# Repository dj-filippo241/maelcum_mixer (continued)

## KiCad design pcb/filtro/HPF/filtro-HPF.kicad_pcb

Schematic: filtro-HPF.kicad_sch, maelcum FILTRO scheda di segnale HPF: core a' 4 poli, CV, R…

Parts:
C1, C2: 220u 35V; CP_Radial_D8.0mm_P3.50mm
C3: 47u 10V; CP_Radial_D5.0mm_P2.00mm
C4, C8: 10u 35V; CP_Radial_D5.0mm_P2.00mm
C5, C9: 47u 35V; CP_Radial_D6.3mm_P2.50mm
C6, C10: 470u 25V; CP_Radial_D8.0mm_P3.50mm
C7, C11: 100u 25V; CP_Radial_D6.3mm_P2.50mm
C12, C13: 1u 50V; C_1206_3216Metric
C14, C15: 1u 25V; C_1206_3216Metric
C16, C17, C19, C20: 4u7 25V; C_1206_3216Metric
C18, C21: 10u 25V; C_1206_3216Metric
C22: 1u; C_1206_3216Metric
C23, C24, C25, C26, C31, C32, C33, C34, C35, C36, C37, C38, C40, C41, C44, C45, C48, C49, C50, C51, C52, C53, C54, C55, C57, C58, C61, C62, C65, C66, C67, C68, C69, C70, C71, C72, C77, C78, C79, C80, C81, C82, C83, C84, C85, C86: 100n; C_0805_2012Metric
C27, C28, C29, C30: 1n C0G; C_1206_3216Metric
C39, C56: 10p C0G; C_0805_2012Metric
C42, C43, C46, C47, C59, C60, C63, C64: 1n1 C0G; C_1206_3216Metric
C73, C75: 22u NP; CP_Radial_D6.3mm_P2.50mm
C74, C76: 47n film; C_1812_4532Metric
D1, D3, D6, D7, D8, D9, D10, D11, D12, D13, D14, D15, D16, D17, D18, D19, D20, D21, D22, D23, D24, D25, D26, D27, D28, D29, D30: 1N4148W; D_SOD-123
D2, D4: S1G; D_SMA
D5: LM4040-5.0; SOT-23
D31, D32, D33, D34: BAT54WS; D_SOD-323
FB1, FB2, FB3, FB4, FB5: ferrite 600R; L_1206_3216Metric
H1, H2, H3: CHASSIS; MountingHole_3.2mm_M3_Pad
J1: C96 maschio; DIN41612_C_3x32_Male_Horizontal_THT
J2: 2x6 cavo piatto; PinHeader_2x06_P2.54mm_Vertical
Q1, Q2, Q3, Q4: THAT320S14-U; SOIC-14_3.9x8.7mm_P1.27mm
Q5, Q6, Q7, Q8: MMBT3906; SOT-23
Q140: BD139; TO-126-3_Vertical
Q141: BD140; TO-126-3_Vertical
R1, R4: 120 1%; R_0805_2012Metric
R2, R5: 1k74 1%; R_0805_2012Metric
R3, R6, R96, R109: 1k; R_0805_2012Metric
R7, R8: 150k 0.1%; R_0805_2012Metric
R9: 1k5; R_0805_2012Metric
R10, R11, R16, R17, R19, R34, R37, R38, R42, R43, R48, R49, R50, R51, R52, R58, R59, R60, R66, R67, R68, R69, R70, R76, R77, R78, R84, R87, R89, R91, R92, R93, R97, R100, R102, R104, R105, R106: 10k 0.1%; R_0805_2012Metric
R12, R41, R95, R108, R110, R111, R112, R113, R114: 100k; R_0805_2012Metric
R13: 9k53 0.1%; R_0805_2012Metric
R14: 17k8 0.1%; R_0805_2012Metric
R15: 21k5 0.1%; R_0805_2012Metric
R18: 8k87 0.1%; R_0805_2012Metric
R20, R32: 24k3 0.1%; R_0805_2012Metric
R21: 1k +3300ppm/K; R_1206_3216Metric
R22, R24, R26, R28: 150 0.1%; R_0805_2012Metric
R23, R25, R27, R29, R86, R99: 2k2; R_0805_2012Metric
R30, R90, R94, R103, R107: 1M; R_0805_2012Metric
R31: 34k 0.1%; R_0805_2012Metric
R33: 113k 0.1%; R_0805_2012Metric
R35: 18k2 0.1%; R_0805_2012Metric
R36: 95k3 0.1%; R_0805_2012Metric
R39: 100k 0.1%; R_0805_2012Metric
R40: 34k8 0.1%; R_0805_2012Metric
R44, R45, R46, R47: 41k7 0.1%; R_0805_2012Metric
R53, R71: 5k41 0.1%; R_0805_2012Metric
R54, R56, R61, R63, R72, R74, R79, R81: 2k87 0.1%; R_0805_2012Metric
R55, R57, R62, R64, R73, R75, R80, R82: 100 0.1%; R_0805_2012Metric
R65, R83: 4k7; R_0805_2012Metric
R85, R98: 20k 0.1%; R_0805_2012Metric
R88, R101: 8k56 0.1%; R_0805_2012Metric
RV1: 1k; Potentiometer_Bourns_3266W_Vertical
RV2: 5k; Potentiometer_Bourns_3266W_Vertical
RV3, RV4, RV5, RV6: 100; Potentiometer_Bourns_3266W_Vertical
RV7: 10k; Potentiometer_Bourns_3266W_Vertical
U1, U8, U9, U14, U15, U20, U21, U22, U23, U24: OPA1654AIDR; SOIC-14_3.9x8.7mm_P1.27mm
U2, U3, U4, U5: LM334SM; SOIC-8_3.9x4.9mm_P1.27mm
U6, U7, U25: OPA1642AIDR; SOIC-8_3.9x4.9mm_P1.27mm
U10, U16, U146: OPA1612AIDR; SOIC-8_3.9x4.9mm_P1.27mm
U11, U12, U13, U17, U18, U19: LM13700M; SOIC-16_3.9x9.9mm_P1.27mm
U26: ADG1434YRUZ; TSSOP-20_4.4x6.5mm_P0.65mm
U140: LM317; TO-220-3_Vertical
U141: LM337; TO-220-3_Vertical
U142: 78L15; SOT-89-3
U143: 79L15; SOT-89-3
U144: LT3045EMSE; MSOP-12-1EP_3x4.039mm_P0.65mm_EP1.651x2.845mm
U145: LT3094EMSE; MSOP-12-1EP_3x4.039mm_P0.65mm_EP1.651x2.845mm

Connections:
+5V: FB5.1, J1.a21, J1.a22
+5VF: C3.1, FB5.2
+15LN: C18.1, C23.1, C25.1, C31.1, C33.1, C35.1, C37.1, C44.1, C48.1, C50.1, C52.1, C54.1, C61.1, C65.1, C67.1, C69.1, C71.1, R9.1, U1.4 (V+), U6.8 (V+), U7.8 (V+), U8.4 (V+), U9.4 (V+), U11.11 (V+), U12.11 (V+), U13.11 (V+), U14.4 (V+), U15.4 (V+), U17.11 (V+), U18.11 (V+), U19.11 (V+), U20.4 (V+), U21.4 (V+), U144.10 (OUTS), U144.11 (OUT), U144.12 (OUT), U146.8 (V+)
+15SW: C14.1, C85.1, U26.16 (VDD), U142.1 (OUT)
+18V: C7.1, C17.1, C40.1, C57.1, C77.1, C79.1, C81.1, C83.1, Q140.1 (E), U10.8 (V+), U16.8 (V+), U22.4 (V+), U23.4 (V+), U24.4 (V+), U25.8 (V+), U144.1 (IN), U144.2 (IN), U144.3 (IN), U144.4 (EN/UV), U144.7 (PGFB)
+REF5: J2.3, J2.12, R10.1, R18.1, R30.2, R36.1, U146.1, U146.2 (-)
-15LN: C21.2, C24.2, C26.2, C32.2, C34.2, C36.2, C38.2, C45.2, C49.2, C51.2, C53.2, C55.2, C62.2, C66.2, C68.2, C70.2, C72.2, RV3.2, RV3.3, RV4.2, RV4.3, RV5.2, RV5.3, RV6.2, RV6.3, U1.11 (V-), U2.1 (V-), U3.1 (V-), U4.1 (V-), U5.1 (V-), U6.4 (V-), U7.4 (V-), U8.11 (V-), U9.11 (V-), U11.6 (V-), U12.6 (V-), U13.6 (V-), U14.11 (V-), U15.11 (V-), U17.6 (V-), U18.6 (V-), U19.6 (V-), U20.11 (V-), U21.11 (V-), U145.10 (OUTS), U145.11 (OUT), U145.12 (OUT), U146.4 (V-)
-15SW: C15.2, C86.2, U26.5 (VSS), U143.3 (VO)
-18V: C11.2, C20.2, C41.2, C58.2, C78.2, C80.2, C82.2, C84.2, Q141.1 (E), U10.4 (V-), U16.4 (V-), U22.11 (V-), U23.11 (V-), U24.11 (V-), U25.4 (V-), U145.1 (IN), U145.2 (IN), U145.3 (EN/UV), U145.5 (PGFB), U145.13 (IN)
-REF5: R11.2, R15.2, R33.2, R35.2, R39.1, U146.7
ADJ+: C4.1, D1.2 (A), R1.2, R2.1, U140.1 (ADJ)
ADJ-: C8.2, D3.1 (K), R4.2, R5.1, U141.1 (ADJ)
AGND: C1.2, C2.1, C4.2, C5.2, C6.2, C7.2, C8.1, C9.1, C10.1, C11.1, C12.2, C13.1, C14.2, C15.1, C16.2, C17.2, C18.2, C19.1, C20.1, C21.1, C22.2, C23.2, C24.1, C25.2, C26.1, C31.2, C32.1, C33.2, C34.1, C35.2, C36.1, C37.2, C38.1, C40.2, C41.1, C42.2, C43.2, C44.2, C45.1, C46.2, C47.2, C48.2, C49.1, C50.2, C51.1, C52.2, C53.1, C54.2, C55.1, C57.2, C58.1, C59.2, C60.2, C61.2, C62.1, C63.2, C64.2, C65.2, C66.1, C67.2, C68.1, C69.2, C70.1, C71.2, C72.1, C77.2, C78.1, C79.2, C80.1, C81.2, C82.1, C83.2, C84.1, C85.2, C86.1, D5.2 (A), D7.2 (A), D8.2 (A), D9.2 (A), D10.2 (A), D24.1 (K), D25.2 (A), D28.1 (K), D29.2 (A), J1.a13, J1.a14, J1.a15, J1.a16, J1.a17, J1.a18, J1.a19, J1.a20, J1.b3, J1.b6, J1.b9, J1.b12, J1.b15, J1.b18, J1.b21, J1.b24, J1.b27, J1.b30, J2.1, J2.5, J2.8, J2.11, Q1.4 (SUB), Q1.6 (B3), Q1.11 (SUB2), Q1.13 (B2), Q2.4 (SUB), Q2.6 (B3), Q2.11 (SUB2), Q2.13 (B2), Q3.4 (SUB), Q3.6 (B3), Q3.11 (SUB2), Q3.13 (B2), Q4.4 (SUB), Q4.6 (B3), Q4.11 (SUB2), Q4.13 (B2), R2.2, R5.2, R7.2, R8.2, R12.2, R21.2, R41.2, R44.2, R45.2, R46.2, R47.2, R55.2, R57.2, R62.2, R64.2, R73.2, R75.2, R80.2, R82.2, R90.2, R96.2, R103.2, R109.2, U1.5 (+), U1.10 (+), U6.3 (+), U6.5 (+), U7.3 (+), U7.5 (+), U8.5 (+), U8.10 (+), U8.12 (+), U10.3 (+), U11.4 (INN_A), U11.13 (INN_B), U12.4 (INN_A), U12.13 (INN_B), U13.4 (INN_A), U13.14 (INP_B), U14.3 (+), U14.12 (+), U15.10 (+), U15.12 (+), U16.3 (+), U17.4 (INN_A), U17.13 (INN_B), U18.4 (INN_A), U18.13 (INN_B), U19.4 (INN_A), U19.14 (INP_B), U20.3 (+), U20.12 (+), U21.10 (+), U21.12 (+), U22.3 (+), U22.10 (+), U23.5 (+), U23.12 (+), U24.10 (+), U24.12 (+), U25.3 (+), U25.5 (+), U26.4 (S1B), U26.6 (GND), U26.7 (S2B), U26.11 (IN3), U26.12 (S3A), U26.13 (D3), U26.14 (S3B), U26.17 (S4B), U26.18 (D4), U26.19 (S4A), U26.20 (IN4), U142.2 (GND), U143.1 (GND), U144.6 (ILIM), U144.9 (GND), U144.13 (GND), U145.6 (ILIM), U145.9 (GND), U146.5 (+)
AL: R85.2, R86.1, U22.1
AR: R98.2, R99.1, U23.7
ARR: D13.1 (K), D14.2 (A), U8.8
BASE+: C6.1, Q140.3 (B), R3.2
BASE-: C10.2, Q141.3 (B), R6.2
BKL1: R56.2, R57.1, U11.14 (INP_B)
BKL2: R63.2, R64.1, U12.14 (INP_B), U13.3 (INP_A), U13.13 (INN_B)
BKR1: R74.2, R75.1, U17.14 (INP_B)
BKR2: R81.2, R82.1, U18.14 (INP_B), U19.3 (INP_A), U19.13 (INN_B)
BPBL1: R53.1, R56.1, U14.6 (-), U14.7
BPBL2: R63.1, R65.1, U15.1, U15.2 (-)
BPBR1: R71.1, R74.1, U20.6 (-), U20.7
BPBR2: R81.1, R83.1, U21.1, U21.2 (-)
BPL1: C42.1, U11.5 (OUT_A), U14.5 (+)
BPL2: C46.1, U12.5 (OUT_A), U15.3 (+)
BPR1: C59.1, U17.5 (OUT_A), U20.5 (+)
BPR2: C63.1, U18.5 (OUT_A), U21.3 (+)
BRNL: Q6.1 (B), U9.7
BRNR: Q8.1 (B), U9.14
BRPL: Q5.1 (B), U9.1
BRPR: Q7.1 (B), U9.8
BUS_HPF_L: C39.2, J1.b1, R48.2, U10.2 (-)
BUS_HPF_R: C56.2, J1.b2, R66.2, U16.2 (-)
CHASSIS: H1.1, H2.1, H3.1, J1.a25, J1.a26
CRL1: C27.2, Q1.1 (C1), U2.3 (V+), U6.2 (-)
CRL2: C28.2, Q2.1 (C1), U3.3 (V+), U6.6 (-)
CRR1: C29.2, Q3.1 (C1), U4.3 (V+), U7.2 (-)
CRR2: C30.2, Q4.1 (C1), U5.3 (V+), U7.6 (-)
CTRL_GND: C3.2, J1.a23, J1.a24, J1.c16, J1.c20, J1.c24, J1.c28, R110.2, R111.2, R112.2, R113.2, R114.2
DNL: R87.2, R88.2, R89.1, U22.9 (-)
DNR: R100.2, R101.2, R102.1, U23.13 (-)
DWL: J2.7, R90.1, U22.12 (+)
DWR: J2.10, R103.1, U24.3 (+)
ERNL: Q6.2 (E), R45.1, U9.6 (-)
ERNR: Q8.2 (E), R47.1, U9.13 (-)
ERPL: Q5.2 (E), R44.1, U9.2 (-)
ERPR: Q7.2 (E), R46.1, U9.9 (-)
EXL1: D7.1 (K), Q1.3 (E1), Q1.5 (E3), Q1.12 (E2), R23.2
EXL2: D8.1 (K), Q2.3 (E1), Q2.5 (E3), Q2.12 (E2), R25.2
EXR1: D9.1 (K), Q3.3 (E1), Q3.5 (E3), Q3.12 (E2), R27.2
EXR2: D10.1 (K), Q4.3 (E1), Q4.5 (E3), Q4.12 (E2), R29.2
FILT_MODE1_0: D31.2 (A), J1.c1, R110.1
FILT_MODE2_0: D32.2 (A), J1.c3, R111.1
FILT_MODE3_0: D33.2 (A), J1.c5, R112.1
FILT_MODE4_0: D34.2 (A), J1.c7, R113.1
FW: J2.2, R12.1, U1.3 (+)
GNL: R84.2, R85.1, U22.2 (-)
GNR: R97.2, R98.1, U23.6 (-)
HKL1: R54.2, R55.1, U11.3 (INP_A)
HKL2: R61.2, R62.1, U12.3 (INP_A)
HKR1: R72.2, R73.1, U17.3 (INP_A)
HKR2: R79.2, R80.1, U18.3 (INP_A)
HPF_OUT_L: J1.b7, R49.2
HPF_OUT_R: J1.b8, R67.2
HPL1: R52.2, R54.1, R58.1, U14.1
HPL2: R60.2, R61.1, R84.1, R87.1, R92.1, U14.14
HPR1: R70.2, R72.1, R76.1, U20.1
HPR2: R78.2, R79.1, R97.1, R100.1, R105.1, U20.14
IAL1_1: Q1.14 (C2), U11.1 (IABC_A)
IAL1_2: Q1.7 (C3), U11.16 (IABC_B)
IAL2_1: Q2.14 (C2), U12.1 (IABC_A)
IAL2_2: Q2.7 (C3), U12.16 (IABC_B)
IAR1_1: Q3.14 (C2), U17.1 (IABC_A)
IAR1_2: Q3.7 (C3), U17.16 (IABC_B)
IAR2_1: Q4.14 (C2), U18.1 (IABC_A)
IAR2_2: Q4.7 (C3), U18.16 (IABC_B)
IRNL: Q6.3 (C), U13.16 (IABC_B)
IRNR: Q8.3 (C), U19.16 (IABC_B)
IRPL: Q5.3 (C), U13.1 (IABC_A)
IRPR: Q7.3 (C), U19.1 (IABC_A)
LPBL1: R51.1, U14.8, U14.9 (-)
LPBL2: R59.1, U15.6 (-), U15.7
LPBR1: R69.1, U20.8, U20.9 (-)
LPBR2: R77.1, U21.6 (-), U21.7
LPL1: C43.1, U11.12 (OUT_B), U14.10 (+)
LPL2: C47.1, U12.12 (OUT_B), U15.5 (+)
LPR1: C60.1, U17.12 (OUT_B), U20.10 (+)
LPR2: C64.1, U18.12 (OUT_B), U21.5 (+)
MUTEN: D31.1 (K), D32.1 (K), D33.1 (K), D34.1 (K), R114.1, U26.1 (IN1), U26.10 (IN2)
N1R: D11.2 (A), R32.2, R33.1
N2R: D12.2 (A), R34.2, R35.1
NHF: D6.2 (A), R14.2, R15.1
NIG: R42.2, R43.1, U8.13 (-)
NLAL: D15.1 (K), D16.2 (A)
NLAR: D19.1 (K), D20.2 (A)
NLBL: D17.1 (K), D18.2 (A)
NLBR: D21.1 (K), D22.2 (A)
NLL: D15.2 (A), D18.1 (K), R65.2
NLR: D19.2 (A), D22.1 (K), R83.2
NREF5I: R10.2, R11.1, U146.6 (-)
NSL1: R50.2, R51.2, R52.1, R53.2, U14.2 (-)
NSL2: D16.1 (K), D17.2 (A), R58.2, R59.2, R60.1, U13.5 (OUT_A), U13.12 (OUT_B), U14.13 (-)
NSR1: R68.2, R69.2, R70.1, R71.2, U20.2 (-)
NSR2: D20.1 (K), D21.2 (A), R76.2, R77.2, R78.1, U19.5 (OUT_A), U19.12 (OUT_B), U20.13 (-)
NU15_1: U15.8, U15.9 (-)
NU15_2: U15.13 (-), U15.14
NU21_1: U21.8, U21.9 (-)
NU21_2: U21.13 (-), U21.14
NU24_1: U24.8, U24.9 (-)
NU24_2: U24.13 (-), U24.14
NWF: R17.2, R19.1, RV1.2, RV1.3, U1.9 (-)
OD_L: R49.1, U10.6 (-), U10.7
OD_R: R67.1, U16.6 (-), U16.7
OLL1: C27.1, R23.1, U6.1
OLL2: C28.1, R25.1, U6.7
OLR1: C29.1, R27.1, U7.1
OLR2: C30.1, R29.1, U7.7
PTL: C73.2, J2.6
PTR: C75.2, J2.9
RAW+22: FB3.1, J1.a5, J1.a6
RAW+27: FB1.1, J1.a1, J1.a2
RAW-22: FB4.1, J1.a7, J1.a8
RAW-27: FB2.1, J1.a3, J1.a4
REF5K: C22.1, D5.1 (K), R9.2, U146.3 (+)
RRF: R36.2, RV7.1
RSF: R20.2, RV2.1
RSL1: R22.1, U2.2 (R)
RSL2: R24.1, U3.2 (R)
RSR1: R26.1, U4.2 (R)
RSR2: R28.1, U5.2 (R)
RTL1: R22.2, RV3.1
RTL2: R24.2, RV4.1
RTR1: R26.2, RV5.1
RTR2: R28.2, RV6.1
RW: J2.4, R30.1, U8.3 (+)
RX_L: C39.1, R48.1, R50.1, U10.1
RX_R: C56.1, R66.1, R68.1, U16.1
RZF: R18.2, RV1.1
SETN: C19.2, R8.1, U145.8 (SET)
SETP: C16.1, R7.1, U144.8 (SET)
SHF: R16.2, R17.1, U1.7
SIL: C74.1, R94.2, U25.2 (-)
SIR: C76.1, R107.2, U25.6 (-)
SJR: D11.1 (K), D12.1 (K), R31.2, R37.1, RV7.2, RV7.3, U8.6 (-)
SNL: R91.2, R92.2, R93.1, U23.2 (-)
SNR: R104.2, R105.2, R106.1, U24.6 (-)
SOL: C74.2, R95.1, U25.1
SOR: C76.2, R108.1, U25.7
SRR: D13.2 (A), R38.2, R39.2, R40.2, U8.9 (-)
V22F+: C12.1, FB3.2, U142.3 (IN)
V22F-: C13.2, FB4.2, U143.2 (VI)
V27F+: C1.1, D2.1 (K), FB1.2, U140.3 (VI)
V27F-: C2.2, D4.2 (A), FB2.2, U141.2 (VI)
VB1: Q1.2 (B1), Q2.2 (B1), Q3.2 (B1), Q4.2 (B1), U1.13 (-), U1.14
VBD: R21.1, RV2.2, RV2.3, U1.12 (+)
VDL: C73.1, R89.2, U22.8
VDR: C75.1, R102.2, U23.14
VGF: D6.1 (K), R13.2, R16.1, U1.6 (-)
VNG: D14.1 (K), R40.1, R41.1, R42.1
VNN: R43.2, U8.14, U9.5 (+), U9.12 (+)
VPL: R95.2, R96.1, U23.3 (+)
VPN: R37.2, U8.7, U9.3 (+), U9.10 (+)
VPR: R108.2, R109.1, U24.5 (+)
VREG+: C5.1, D1.1 (K), D2.2 (A), Q140.2 (C), R1.1, R3.1, U140.2 (VO)
VREG-: C9.2, D3.2 (A), D4.1 (K), Q141.2 (C), R4.1, R6.1, U141.3 (VO)
VXF: R13.1, R14.1, U1.1, U1.2 (-)
VXR: R31.1, R32.1, R34.1, R38.1, U8.1, U8.2 (-)
WBL: R88.1, U22.6 (-), U22.7
WBR: R101.1, U23.8, U23.9 (-)
WF: R19.2, R20.1, U1.8
WL: D23.2 (A), D26.1 (K), R86.2, U22.5 (+)
WOL: R91.1, U22.13 (-), U22.14
WOR: R104.1, U24.1, U24.2 (-)
WPL: D23.1 (K), D24.2 (A)
WPR: D27.1 (K), D28.2 (A)
WQL: D25.1 (K), D26.2 (A)
WQR: D29.1 (K), D30.2 (A)
WR: D27.2 (A), D30.1 (K), R99.2, U23.10 (+)
YL: R93.2, R94.1, U23.1, U26.2 (S1A)
YM_L: U10.5 (+), U26.3 (D1)
YM_R: U16.5 (+), U26.8 (D2)
YR: R106.2, R107.1, U24.7, U26.9 (S2A)

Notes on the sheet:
BACKPLANE C96 (classe FILTRO, sistema-backplane §4, dec. 159)
ALIMENTAZIONE +-18 audio, +-15 switch, +5, +-15 LN (core e CV), +-5 riferimento
FREQ: buffer del pot, shaper (sistema-shaper §3), offset, partitore tempco (RISULTATI-conv-that320)
CONVERTER ESPONENZIALI: THAT 320 + LM334 PTAT, uno per sezione 2 poli (RISULTATI-conv-that320)
RES dec. 153: shaper gpos, raddrizzatore gneg, sorgenti P e N (filter-module §5, shaper-res.cir)
RICEVITORE del bus e CORE (a') 4 poli, lato L (d5c-sum-pass-hp.cir)
RICEVITORE del bus e CORE (a') 4 poli, lato R (d5c-sum-pass-hp.cir)
OVERDRIVE v0.2 col DRIVE a pot doppio e servo DC (§5ter, od2-pot-tran.cir, od2-servo-dc.cir)
MUTO della sezione (bit FILT_MODE, §2bis) e driver verso il DJ bus
CAVO SCHEDA COMANDI (J2)

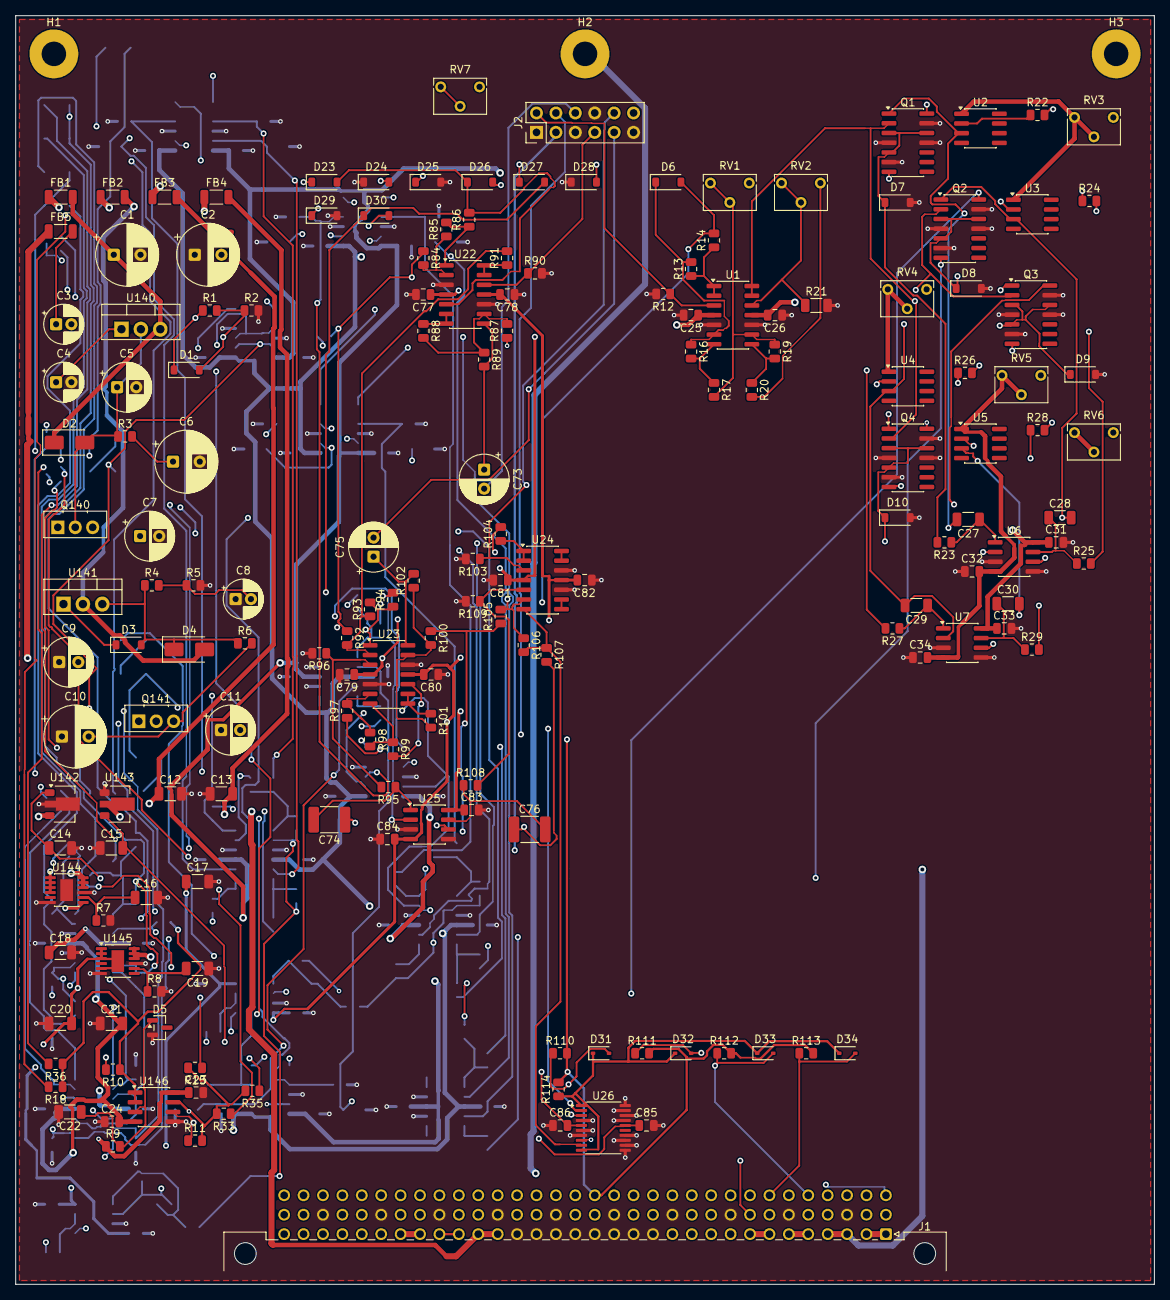
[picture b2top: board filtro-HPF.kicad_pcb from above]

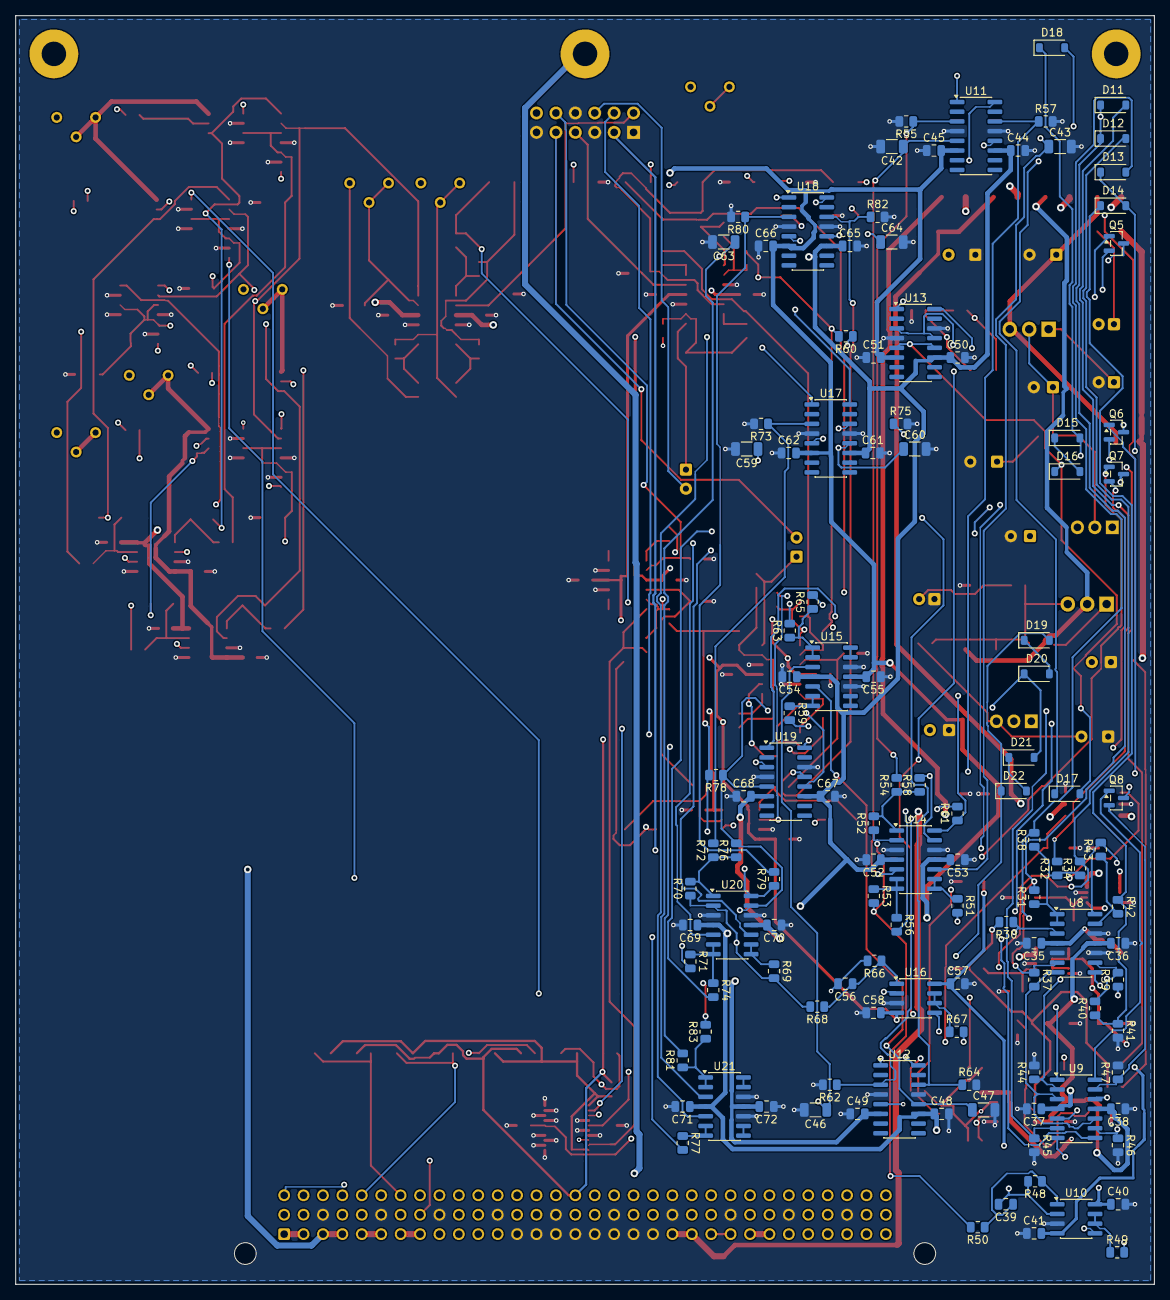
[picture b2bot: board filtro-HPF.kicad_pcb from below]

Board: 4 copper layers, 149.0 x 166.0 mm, 294 parts (119 on the bottom side), 185 nets.

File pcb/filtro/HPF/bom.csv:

quantita;valore;impronta;riferimenti;nota
2;220u 35V;CP_Radial_D8.0mm_P3.50mm;C1 C2;
2;1u 50V;C_1206_3216Metric;C12 C13;
2;1u 25V;C_1206_3216Metric;C14 C15;
1;4u7 25V;C_1206_3216Metric;C16;rumore del riferimento (datasheet: 4,7 uF)
3;4u7 25V;C_1206_3216Metric;C17 C19 C20;
2;10u 25V;C_1206_3216Metric;C18 C21;
1;1u;C_1206_3216Metric;C22;
46;100n;C_0805_2012Metric;C23 C24 C25 C26 C31 C32 C33 C34 C35 C36 C37 C38 C40 C41 C44 C45 C48 C49 C50 C51 C52 C53 C54 C55 C57 C58 C61 C62 C65 C66 C67 C68 C69 C70 C71 C72 C77 C78 C79 C80 C81 C82 C83 C84 C85 C86;
4;1n C0G;C_1206_3216Metric;C27 C28 C29 C30;compensazione dell'anello (taglio ~72 kHz)
1;47u 10V;CP_Radial_D5.0mm_P2.00mm;C3;
2;10p C0G;C_0805_2012Metric;C39 C56;
2;10u 35V;CP_Radial_D5.0mm_P2.00mm;C4 C8;
4;1n1 C0G;C_1206_3216Metric;C42 C46 C59 C63;C 33n x k, C0G 1 % appaiati (§5quater)
4;1n1 C0G;C_1206_3216Metric;C43 C47 C60 C64;
2;47u 35V;CP_Radial_D6.3mm_P2.50mm;C5 C9;
2;470u 25V;CP_Radial_D8.0mm_P3.50mm;C6 C10;
2;100u 25V;CP_Radial_D6.3mm_P2.50mm;C7 C11;
2;22u NP;CP_Radial_D6.3mm_P2.50mm;C73 C75;niente continua sul pot (taglio 0,7 Hz)
2;47n film;C_1812_4532Metric;C74 C76;
1;1N4148W;D_SOD-123;D1;scarica Cadj
1;S1G;D_SMA;D2;protezione inversa
22;1N4148W;D_SOD-123;D3 D6 D11 D12 D13 D14 D15 D16 D17 D18 D19 D20 D21 D22 D23 D24 D25 D26 D27 D28 D29 D30;
4;BAT54WS;D_SOD-323;D31 D32 D33 D34;OR: la sezione suona se almeno un canale la sceglie
1;S1G;D_SMA;D4;
1;LM4040-5.0;SOT-23;D5;
4;1N4148W;D_SOD-123;D7 D8 D9 D10;protegge la giunzione E-B all'accensione
5;ferrite 600R;L_1206_3216Metric;FB1 FB2 FB3 FB4 FB5;
1;C96 maschio;DIN41612_C_3x32_Male_Horizontal_THT;J1;DIN 41612 C 3x32, angolo retto; sezione HPF del filtro
1;2x6 cavo piatto;PinHeader_2x06_P2.54mm_Vertical;J2;cavo piatto corto verso la scheda comandi dietro il pannello (dec. 133)
1;THAT320S14-U;SOIC-14_3.9x8.7mm_P1.27mm;Q1;Q1 riferimento, Q2 e Q3 verso i pin Iabc della sezione 1, lato L; Q4 libero
1;BD139;TO-126-3_Vertical;Q140;
1;BD140;TO-126-3_Vertical;Q141;
1;THAT320S14-U;SOIC-14_3.9x8.7mm_P1.27mm;Q2;Q1 riferimento, Q2 e Q3 verso i pin Iabc della sezione 2, lato L; Q4 libero
1;THAT320S14-U;SOIC-14_3.9x8.7mm_P1.27mm;Q3;Q1 riferimento, Q2 e Q3 verso i pin Iabc della sezione 1, lato R; Q4 libero
1;THAT320S14-U;SOIC-14_3.9x8.7mm_P1.27mm;Q4;Q1 riferimento, Q2 e Q3 verso i pin Iabc della sezione 2, lato R; Q4 libero
1;MMBT3906;SOT-23;Q5;sorgente: spinge Iabc nel pin dell'OTA PL
1;MMBT3906;SOT-23;Q6;sorgente: spinge Iabc nel pin dell'OTA NL
1;MMBT3906;SOT-23;Q7;sorgente: spinge Iabc nel pin dell'OTA PR
1;MMBT3906;SOT-23;Q8;sorgente: spinge Iabc nel pin dell'OTA NR
2;120 1%;R_0805_2012Metric;R1 R4;
31;10k 0.1%;R_0805_2012Metric;R10 R11 R16 R17 R19 R34 R37 R38 R43 R50 R51 R52 R58 R59 R60 R68 R69 R70 R76 R77 R78 R84 R87 R89 R91 R92 R97 R100 R102 R104 R105;
4;100k;R_0805_2012Metric;R110 R111 R112 R113;pull-down lato filtro (sistema-backplane §5)
1;100k;R_0805_2012Metric;R12;pot staccato = inizio corsa
1;9k53 0.1%;R_0805_2012Metric;R13;shaper-filtro-freq-hpf.cir
1;17k8 0.1%;R_0805_2012Metric;R14;
1;21k5 0.1%;R_0805_2012Metric;R15;
1;8k87 0.1%;R_0805_2012Metric;R18;offset 5,40 V: 9,26k = 8,87k + trimmer (zero)
1;1k74 1%;R_0805_2012Metric;R2;E96 1,74k = 19,4 V (fx-send NOTE punto 16)
1;24k3 0.1%;R_0805_2012Metric;R20;26,7k = 24,3k + trimmer (scala, ottave)
1;1k +3300ppm/K;R_1206_3216Metric;R21;NOTA: tempco +3300 ppm/K, incollata ai THAT 320 (RISULTATI-conv-that320)
4;150 0.1%;R_0805_2012Metric;R22 R24 R26 R28;
4;2k2;R_0805_2012Metric;R23 R25 R27 R29;
1;1k;R_0805_2012Metric;R3;NOTA: cap-moltiplicatore come il FX-SEND (~50 mA)
1;1M;R_0805_2012Metric;R30;pot staccato = RES a zero (manopola rovescia: Vx 5 V)
1;34k 0.1%;R_0805_2012Metric;R31;
1;24k3 0.1%;R_0805_2012Metric;R32;
1;113k 0.1%;R_0805_2012Metric;R33;
1;18k2 0.1%;R_0805_2012Metric;R35;
1;95k3 0.1%;R_0805_2012Metric;R36;Rref 102k = 95,3k + trimmer: il fischio parte al 93 %
1;100k 0.1%;R_0805_2012Metric;R39;soglia 0,5 V
1;34k8 0.1%;R_0805_2012Metric;R40;
4;100k;R_0805_2012Metric;R41 R95 R108 R114;
1;10k 0.1%;R_0805_2012Metric;R42;NOTA: invertitore, la sorgente PNP vuole un comando negativo
4;41k7 0.1%;R_0805_2012Metric;R44 R45 R46 R47;NOTA: 5 V = 119,7 uA = gres 1 sulla sezione Q 1,307 (d5b-4p: 22,6k x 1,848)
2;10k 0.1%;R_0805_2012Metric;R48 R66;ricevitore a massa virtuale (sistema-backplane §4)
2;10k 0.1%;R_0805_2012Metric;R49 R67;R lato sorgente sul DJ bus (dec. 159)
1;1k74 1%;R_0805_2012Metric;R5;
2;5k41 0.1%;R_0805_2012Metric;R53 R71;NOTA: Q 0,541 con una R (d = 1,848) al posto dell'OTA a Iabc fissa del sim
8;2k87 0.1%;R_0805_2012Metric;R54 R56 R61 R63 R72 R74 R79 R81;
8;100 0.1%;R_0805_2012Metric;R55 R57 R62 R64 R73 R75 R80 R82;
3;1k;R_0805_2012Metric;R6 R96 R109;
2;4k7;R_0805_2012Metric;R65 R83;limitatore (§5quater, d5a-res153-osc.cir)
2;150k 0.1%;R_0805_2012Metric;R7 R8;
2;20k 0.1%;R_0805_2012Metric;R85 R98;
2;2k2;R_0805_2012Metric;R86 R99;tosatore: 2+2 1N4148 a massa
2;8k56 0.1%;R_0805_2012Metric;R88 R101;10k/k, k 1,171 (E192 8,56k: k 1,168)
1;1k5;R_0805_2012Metric;R9;NOTA: ~6,7 mA nel riferimento (come il master)
2;1M;R_0805_2012Metric;R90 R103;pot staccato = DRIVE a zero
2;10k 0.1%;R_0805_2012Metric;R93 R106;y = -(x + m d)
2;1M;R_0805_2012Metric;R94 R107;servo DC: integratore 1M / 47n, polo 0,05 Hz
1;1k;Potentiometer_Bourns_3266W_Vertical;RV1;ZERO della frequenza (RISULTATI-conv-that320)
1;5k;Potentiometer_Bourns_3266W_Vertical;RV2;SCALA della frequenza
4;100;Potentiometer_Bourns_3266W_Vertical;RV3 RV4 RV5 RV6;fondo scala del converter (Iref 271-451 uA)
1;10k;Potentiometer_Bourns_3266W_Vertical;RV7;taratura della RES: «il fischio parte al 93 %»
1;OPA1654AIDR;SOIC-14_3.9x8.7mm_P1.27mm;U1;FREQ: buffer del pot, shaper, offset, buffer della base dei Q1
1;OPA1612AIDR;SOIC-8_3.9x4.9mm_P1.27mm;U10;ricevitore del bus (A) e driver d'uscita (B), lato L
1;LM13700M;SOIC-16_3.9x9.9mm_P1.27mm;U11;integratori della sezione 1, lato L
1;LM13700M;SOIC-16_3.9x9.9mm_P1.27mm;U12;integratori della sezione 2, lato L
2;LM13700M;SOIC-16_3.9x9.9mm_P1.27mm;U13 U19;RES: OTA P smorza, OTA N innesca (gres = gpos - gneg)
2;OPA1654AIDR;SOIC-14_3.9x8.7mm_P1.27mm;U14 U15;core lato L: summer e buffer di stato
1;LM317;TO-220-3_Vertical;U140;
1;LM337;TO-220-3_Vertical;U141;
1;78L15;SOT-89-3;U142;
1;79L15;SOT-89-3;U143;
1;LT3045EMSE;MSOP-12-1EP_3x4.039mm_P0.65mm_EP1.651x2.845mm;U144;EN/UV a IN; ILIM a massa; PG libero; PGFB a IN (come master-segnale.py)
1;LT3094EMSE;MSOP-12-1EP_3x4.039mm_P0.65mm_EP1.651x2.845mm;U145;EN/UV a IN; PG libero; PGFB a IN; ILIM a massa; VIOC libero
1;OPA1612AIDR;SOIC-8_3.9x4.9mm_P1.27mm;U146;+5 e -5 V di riferimento
1;OPA1612AIDR;SOIC-8_3.9x4.9mm_P1.27mm;U16;ricevitore del bus (A) e driver d'uscita (B), lato R
1;LM13700M;SOIC-16_3.9x9.9mm_P1.27mm;U17;integratori della sezione 1, lato R
1;LM13700M;SOIC-16_3.9x9.9mm_P1.27mm;U18;integratori della sezione 2, lato R
4;LM334SM;SOIC-8_3.9x4.9mm_P1.27mm;U2 U3 U4 U5;Iref PTAT dal collettore di Q1 verso -15 V (filter-module §4, todo 50)
2;OPA1654AIDR;SOIC-14_3.9x8.7mm_P1.27mm;U20 U21;core lato R: summer e buffer di stato
3;OPA1654AIDR;SOIC-14_3.9x8.7mm_P1.27mm;U22 U23 U24;overdrive: x2, buffer del tosatore, differenza, buffer del cursore, I/V
1;OPA1642AIDR;SOIC-8_3.9x4.9mm_P1.27mm;U25;servo DC dell'overdrive (FET)
1;ADG1434YRUZ;TSSOP-20_4.4x6.5mm_P0.65mm;U26;NOTA: muto secco (A = IN alto = suona, B = massa); il fischio della RES tagliato puo' fare click
2;OPA1642AIDR;SOIC-8_3.9x4.9mm_P1.27mm;U6 U7;anelli dei converter (FET: niente corrente nel nodo cr)
2;OPA1654AIDR;SOIC-14_3.9x8.7mm_P1.27mm;U8 U9;RES: buffer del pot, shaper, raddrizzatore, invertitore, 4 sorgenti

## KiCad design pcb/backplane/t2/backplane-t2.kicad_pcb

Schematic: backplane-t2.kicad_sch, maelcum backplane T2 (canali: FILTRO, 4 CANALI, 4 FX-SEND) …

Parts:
C1, C3, C5, C7, C9, C11, C13, C15, C17, C19, C21, C23, C25, C27, C29, C31, C33, C35, C37, C39, C41, C43, C45, C47, C49, C51, C53, C55, C57, C59, C61, C63, C65, C67, C69, C71, C73, C75, C77, C79, C81, C83, C85, C87, C89, C91, C93, C95, C97, C99: 100n 50V; C_0805_2012Metric
C2, C4, C6, C8, C10, C12, C14, C16, C18, C20, C22, C24, C26, C28, C30, C32, C34, C36, C38, C40, C42, C44, C46, C48, C50, C52, C54, C56, C58, C60, C62, C64, C66, C68, C70, C72, C74, C76, C78, C80, C82, C84, C86, C88, C90, C92, C94, C96, C98, C100: 10u 50V X7R; C_1206_3216Metric
F1, F11, F21, F31: PTC 0.2 A; Fuse_1812_4532Metric
F2, F4, F8, F10, F12, F14, F18, F20, F22, F24, F28, F30, F32, F34, F38, F40, F41, F46: PTC 0.1 A; Fuse_1812_4532Metric
F3, F5, F13, F15, F23, F25, F33, F35, F42, F43, F44, F45, F47, F48, F49, F50: PTC 0.3 A; Fuse_1812_4532Metric
F6, F7, F9, F16, F17, F19, F26, F27, F29, F36, F37, F39: PTC 0.05 A; Fuse_1812_4532Metric
H1, H2, H3, H4, H5: CHASSIS; MountingHole_3.2mm_M3_Pad
JC1: cavo C1 T1-T2 (VE); IDC-Header_2x05_P2.54mm_Vertical
JC2: cavo C2 T1-T2 (pilotato); IDC-Header_2x05_P2.54mm_Vertical
JC3: cavo C3 T2-T3 (pilotato); IDC-Header_2x11_P2.54mm_Vertical
JC4: cavo C4 T2-T4 (VE); IDC-Header_2x09_P2.54mm_Vertical
JCH1: C96 femmina CH1; DIN41612_C_3x32_Female_Vertical_THT
JCH2: C96 femmina CH2; DIN41612_C_3x32_Female_Vertical_THT
JCH3: C96 femmina CH3; DIN41612_C_3x32_Female_Vertical_THT
JCH4: C96 femmina CH4; DIN41612_C_3x32_Female_Vertical_THT
JFIL1: C96 femmina FIL1; DIN41612_C_3x32_Female_Vertical_THT
JFIL2: C96 femmina FIL2; DIN41612_C_3x32_Female_Vertical_THT
JP2: potenza P2 T1-T2; Molex_Mini-Fit_Jr_5566-10A2_2x05_P4.20mm_Vertical
JSEND1: C96 femmina SEND1; DIN41612_C_3x32_Female_Vertical_THT
JSEND2: C96 femmina SEND2; DIN41612_C_3x32_Female_Vertical_THT
JSEND3: C96 femmina SEND3; DIN41612_C_3x32_Female_Vertical_THT
JSEND4: C96 femmina SEND4; DIN41612_C_3x32_Female_Vertical_THT

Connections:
+5V: F1.1, F6.1, F11.1, F16.1, F21.1, F26.1, F31.1, F36.1, F41.1, F46.1, JP2.5
+5V_CH1: C1.1, C2.1, F1.2, JCH1.a21, JCH1.a22
+5V_CH2: C21.1, C22.1, F11.2, JCH2.a21, JCH2.a22
+5V_CH3: C41.1, C42.1, F21.2, JCH3.a21, JCH3.a22
+5V_CH4: C61.1, C62.1, F31.2, JCH4.a21, JCH4.a22
+5V_FIL1: C81.1, C82.1, F41.2, JFIL1.a21, JFIL1.a22
+5V_FIL2: C91.1, C92.1, F46.2, JFIL2.a21, JFIL2.a22
+5V_SEND1: C11.1, C12.1, F6.2, JSEND1.a21, JSEND1.a22
+5V_SEND2: C31.1, C32.1, F16.2, JSEND2.a21, JSEND2.a22
+5V_SEND3: C51.1, C52.1, F26.2, JSEND3.a21, JSEND3.a22
+5V_SEND4: C71.1, C72.1, F36.2, JSEND4.a21, JSEND4.a22
AGND: C1.2, C2.2, C3.2, C4.2, C5.2, C6.2, C7.1, C8.1, C9.1, C10.1, C11.2, C12.2, C13.2, C14.2, C15.2, C16.2, C17.1, C18.1, C19.1, C20.1, C21.2, C22.2, C23.2, C24.2, C25.2, C26.2, C27.1, C28.1, C29.1, C30.1, C31.2, C32.2, C33.2, C34.2, C35.2, C36.2, C37.1, C38.1, C39.1, C40.1, C41.2, C42.2, C43.2, C44.2, C45.2, C46.2, C47.1, C48.1, C49.1, C50.1, C51.2, C52.2, C53.2, C54.2, C55.2, C56.2, C57.1, C58.1, C59.1, C60.1, C61.2, C62.2, C63.2, C64.2, C65.2, C66.2, C67.1, C68.1, C69.1, C70.1, C71.2, C72.2, C73.2, C74.2, C75.2, C76.2, C77.1, C78.1, C79.1, C80.1, C81.2, C82.2, C83.2, C84.2, C85.2, C86.2, C87.1, C88.1, C89.1, C90.1, C91.2, C92.2, C93.2, C94.2, C95.2, C96.2, C97.1, C98.1, C99.1, C100.1, JC1.1, JC1.3, JC1.5, JC1.6, JC1.7, JC1.8, JC1.9, JC1.10, JC2.1, JC2.3, JC2.7, JC2.8, JC2.9, JC2.10, JC3.1, JC3.3, JC3.5, JC3.7, JC3.9, JC3.11, JC3.13, JC3.15, JC3.17, JC3.19, JC3.21, JC3.22, JC4.1, JC4.3, JC4.5, JC4.7, JC4.9, JC4.11, JC4.13, JC4.15, JC4.17, JC4.18, JCH1.a13, JCH1.a14, JCH1.a15, JCH1.a16, JCH1.a17, JCH1.a18, JCH1.a19, JCH1.a20, JCH1.b3, JCH1.b6, JCH1.b9, JCH1.b12, JCH1.b15, JCH1.b18, JCH1.b21, JCH1.b24, JCH1.b27, JCH1.b30, JCH2.a13, JCH2.a14, JCH2.a15, JCH2.a16, JCH2.a17, JCH2.a18, JCH2.a19, JCH2.a20, JCH2.b3, JCH2.b6, JCH2.b9, JCH2.b12, JCH2.b15, JCH2.b18, JCH2.b21, JCH2.b24, JCH2.b27, JCH2.b30, JCH3.a13, JCH3.a14, JCH3.a15, JCH3.a16, JCH3.a17, JCH3.a18, JCH3.a19, JCH3.a20, JCH3.b3, JCH3.b6, JCH3.b9, JCH3.b12, JCH3.b15, JCH3.b18, JCH3.b21, JCH3.b24, JCH3.b27, JCH3.b30, JCH4.a13, JCH4.a14, JCH4.a15, JCH4.a16, JCH4.a17, JCH4.a18, JCH4.a19, JCH4.a20, JCH4.b3, JCH4.b6, JCH4.b9, JCH4.b12, JCH4.b15, JCH4.b18, JCH4.b21, JCH4.b24, JCH4.b27, JCH4.b30, JFIL1.a13, JFIL1.a14, JFIL1.a15, JFIL1.a16, JFIL1.a17, JFIL1.a18, JFIL1.a19, JFIL1.a20, JFIL1.b3, JFIL1.b6, JFIL1.b9, JFIL1.b12, JFIL1.b15, JFIL1.b18, JFIL1.b21, JFIL1.b24, JFIL1.b27, JFIL1.b30, JFIL2.a13, JFIL2.a14, JFIL2.a15, JFIL2.a16, JFIL2.a17, JFIL2.a18, JFIL2.a19, JFIL2.a20, JFIL2.b3, JFIL2.b6, JFIL2.b9, JFIL2.b12, JFIL2.b15, JFIL2.b18, JFIL2.b21, JFIL2.b24, JFIL2.b27, JFIL2.b30, JP2.6, JP2.7, JP2.8, JSEND1.a13, JSEND1.a14, JSEND1.a15, JSEND1.a16, JSEND1.a17, JSEND1.a18, JSEND1.a19, JSEND1.a20, JSEND1.b3, JSEND1.b6, JSEND1.b9, JSEND1.b12, JSEND1.b15, JSEND1.b18, JSEND1.b21, JSEND1.b24, JSEND1.b27, JSEND1.b30, JSEND2.a13, JSEND2.a14, JSEND2.a15, JSEND2.a16, JSEND2.a17, JSEND2.a18, JSEND2.a19, JSEND2.a20, JSEND2.b3, JSEND2.b6, JSEND2.b9, JSEND2.b12, JSEND2.b15, JSEND2.b18, JSEND2.b21, JSEND2.b24, JSEND2.b27, JSEND2.b30, JSEND3.a13, JSEND3.a14, JSEND3.a15, JSEND3.a16, JSEND3.a17, JSEND3.a18, JSEND3.a19, JSEND3.a20, JSEND3.b3, JSEND3.b6, JSEND3.b9, JSEND3.b12, JSEND3.b15, JSEND3.b18, JSEND3.b21, JSEND3.b24, JSEND3.b27, JSEND3.b30, JSEND4.a13, JSEND4.a14, JSEND4.a15, JSEND4.a16, JSEND4.a17, JSEND4.a18, JSEND4.a19, JSEND4.a20, JSEND4.b3, JSEND4.b6, JSEND4.b9, JSEND4.b12, JSEND4.b15, JSEND4.b18, JSEND4.b21, JSEND4.b24, JSEND4.b27, JSEND4.b30
BUS_HPF_L: JCH1.b10, JCH2.b10, JCH3.b10, JCH4.b10, JFIL1.b1
BUS_HPF_R: JCH1.b11, JCH2.b11, JCH3.b11, JCH4.b11, JFIL1.b2
BUS_LPF_L: JCH1.b13, JCH2.b13, JCH3.b13, JCH4.b13, JFIL2.b4
BUS_LPF_R: JCH1.b14, JCH2.b14, JCH3.b14, JCH4.b14, JFIL2.b5
CHASSIS: H1.1, H2.1, H3.1, H4.1, H5.1, JCH1.a25, JCH1.a26, JCH2.a25, JCH2.a26, JCH3.a25, JCH3.a26, JCH4.a25, JCH4.a26, JFIL1.a25, JFIL1.a26, JFIL2.a25, JFIL2.a26, JP2.10, JSEND1.a25, JSEND1.a26, JSEND2.a25, JSEND2.a26, JSEND3.a25, JSEND3.a26, JSEND4.a25, JSEND4.a26
CTRL_GND: JC2.5, JCH1.a23, JCH1.a24, JCH1.c16, JCH1.c20, JCH1.c24, JCH1.c28, JCH2.a23, JCH2.a24, JCH2.c16, JCH2.c20, JCH2.c24, JCH2.c28, JCH3.a23, JCH3.a24, JCH3.c16, JCH3.c20, JCH3.c24, JCH3.c28, JCH4.a23, JCH4.a24, JCH4.c16, JCH4.c20, JCH4.c24, JCH4.c28, JFIL1.a23, JFIL1.a24, JFIL1.c16, JFIL1.c20, JFIL1.c24, JFIL1.c28, JFIL2.a23, JFIL2.a24, JFIL2.c16, JFIL2.c20, JFIL2.c24, JFIL2.c28, JP2.9, JSEND1.a23, JSEND1.a24, JSEND1.c16, JSEND1.c20, JSEND1.c24, JSEND1.c28, JSEND2.a23, JSEND2.a24, JSEND2.c16, JSEND2.c20, JSEND2.c24, JSEND2.c28, JSEND3.a23, JSEND3.a24, JSEND3.c16, JSEND3.c20, JSEND3.c24, JSEND3.c28, JSEND4.a23, JSEND4.a24, JSEND4.c16, JSEND4.c20, JSEND4.c24, JSEND4.c28
CUE1_L: JC3.2, JCH1.b4
CUE1_R: JC3.4, JCH1.b5
CUE2_L: JC3.6, JCH2.b4
CUE2_R: JC3.8, JCH2.b5
CUE3_L: JC3.10, JCH3.b4
CUE3_R: JC3.12, JCH3.b5
CUE4_L: JC3.14, JCH4.b4
CUE4_R: JC3.16, JCH4.b5
DJBUS_L: JC1.2, JCH1.b1, JCH2.b1, JCH3.b1, JCH4.b1, JFIL1.b7, JFIL2.b10
DJBUS_R: JC1.4, JCH1.b2, JCH2.b2, JCH3.b2, JCH4.b2, JFIL1.b8, JFIL2.b11
FILT_MODE1_0: JCH1.c1, JFIL1.c1
FILT_MODE1_1: JCH1.c2, JFIL2.c2
FILT_MODE2_0: JCH2.c1, JFIL1.c3
FILT_MODE2_1: JCH2.c2, JFIL2.c4
FILT_MODE3_0: JCH3.c1, JFIL1.c5
FILT_MODE3_1: JCH3.c2, JFIL2.c6
FILT_MODE4_0: JCH4.c1, JFIL1.c7
FILT_MODE4_1: JCH4.c2, JFIL2.c8
GLOBAL_MUTE: JC2.6, JSEND1.c9, JSEND2.c9, JSEND3.c9, JSEND4.c9
MON_L: JC2.2, JC3.18
MON_R: JC2.4, JC3.20
RAW+22: F2.1, F7.1, F12.1, F17.1, F22.1, F27.1, F32.1, F37.1, F42.1, F47.1, JP2.3
RAW+22_CH1: C3.1, C4.1, F2.2, JCH1.a5, JCH1.a6
RAW+22_CH2: C23.1, C24.1, F12.2, JCH2.a5, JCH2.a6
RAW+22_CH3: C43.1, C44.1, F22.2, JCH3.a5, JCH3.a6
RAW+22_CH4: C63.1, C64.1, F32.2, JCH4.a5, JCH4.a6
RAW+22_FIL1: C83.1, C84.1, F42.2, JFIL1.a5, JFIL1.a6
RAW+22_FIL2: C93.1, C94.1, F47.2, JFIL2.a5, JFIL2.a6
RAW+22_SEND1: C13.1, C14.1, F7.2, JSEND1.a5, JSEND1.a6
RAW+22_SEND2: C33.1, C34.1, F17.2, JSEND2.a5, JSEND2.a6
RAW+22_SEND3: C53.1, C54.1, F27.2, JSEND3.a5, JSEND3.a6
RAW+22_SEND4: C73.1, C74.1, F37.2, JSEND4.a5, JSEND4.a6
RAW+27: F3.1, F8.1, F13.1, F18.1, F23.1, F28.1, F33.1, F38.1, F43.1, F48.1, JP2.1
RAW+27_CH1: C5.1, C6.1, F3.2, JCH1.a1, JCH1.a2
RAW+27_CH2: C25.1, C26.1, F13.2, JCH2.a1, JCH2.a2
RAW+27_CH3: C45.1, C46.1, F23.2, JCH3.a1, JCH3.a2
RAW+27_CH4: C65.1, C66.1, F33.2, JCH4.a1, JCH4.a2
RAW+27_FIL1: C85.1, C86.1, F43.2, JFIL1.a1, JFIL1.a2
RAW+27_FIL2: C95.1, C96.1, F48.2, JFIL2.a1, JFIL2.a2
RAW+27_SEND1: C15.1, C16.1, F8.2, JSEND1.a1, JSEND1.a2
RAW+27_SEND2: C35.1, C36.1, F18.2, JSEND2.a1, JSEND2.a2
RAW+27_SEND3: C55.1, C56.1, F28.2, JSEND3.a1, JSEND3.a2
RAW+27_SEND4: C75.1, C76.1, F38.2, JSEND4.a1, JSEND4.a2
RAW-22: F4.1, F9.1, F14.1, F19.1, F24.1, F29.1, F34.1, F39.1, F44.1, F49.1, JP2.4
RAW-22_CH1: C7.2, C8.2, F4.2, JCH1.a7, JCH1.a8
RAW-22_CH2: C27.2, C28.2, F14.2, JCH2.a7, JCH2.a8
RAW-22_CH3: C47.2, C48.2, F24.2, JCH3.a7, JCH3.a8
RAW-22_CH4: C67.2, C68.2, F34.2, JCH4.a7, JCH4.a8
RAW-22_FIL1: C87.2, C88.2, F44.2, JFIL1.a7, JFIL1.a8
RAW-22_FIL2: C97.2, C98.2, F49.2, JFIL2.a7, JFIL2.a8
RAW-22_SEND1: C17.2, C18.2, F9.2, JSEND1.a7, JSEND1.a8
RAW-22_SEND2: C37.2, C38.2, F19.2, JSEND2.a7, JSEND2.a8
RAW-22_SEND3: C57.2, C58.2, F29.2, JSEND3.a7, JSEND3.a8
RAW-22_SEND4: C77.2, C78.2, F39.2, JSEND4.a7, JSEND4.a8
RAW-27: F5.1, F10.1, F15.1, F20.1, F25.1, F30.1, F35.1, F40.1, F45.1, F50.1, JP2.2
RAW-27_CH1: C9.2, C10.2, F5.2, JCH1.a3, JCH1.a4
RAW-27_CH2: C29.2, C30.2, F15.2, JCH2.a3, JCH2.a4
RAW-27_CH3: C49.2, C50.2, F25.2, JCH3.a3, JCH3.a4
RAW-27_CH4: C69.2, C70.2, F35.2, JCH4.a3, JCH4.a4
RAW-27_FIL1: C89.2, C90.2, F45.2, JFIL1.a3, JFIL1.a4
RAW-27_FIL2: C99.2, C100.2, F50.2, JFIL2.a3, JFIL2.a4
RAW-27_SEND1: C19.2, C20.2, F10.2, JSEND1.a3, JSEND1.a4
RAW-27_SEND2: C39.2, C40.2, F20.2, JSEND2.a3, JSEND2.a4
RAW-27_SEND3: C59.2, C60.2, F30.2, JSEND3.a3, JSEND3.a4
RAW-27_SEND4: C79.2, C80.2, F40.2, JSEND4.a3, JSEND4.a4
S1_L: JC4.2, JSEND1.b4, JSEND2.b4, JSEND3.b4, JSEND4.b4
S1_R: JC4.4, JSEND1.b5, JSEND2.b5, JSEND3.b5, JSEND4.b5
S2_L: JC4.6, JSEND1.b7, JSEND2.b7, JSEND3.b7, JSEND4.b7
S2_R: JC4.8, JSEND1.b8, JSEND2.b8, JSEND3.b8, JSEND4.b8
S3_L: JC4.10, JSEND1.b10, JSEND2.b10, JSEND3.b10, JSEND4.b10
S3_R: JC4.12, JSEND1.b11, JSEND2.b11, JSEND3.b11, JSEND4.b11
S4_L: JC4.14, JSEND1.b13, JSEND2.b13, JSEND3.b13, JSEND4.b13
S4_R: JC4.16, JSEND1.b14, JSEND2.b14, JSEND3.b14, JSEND4.b14
SEND_TAP1_L: JCH1.b7, JSEND1.b1
SEND_TAP1_R: JCH1.b8, JSEND1.b2
SEND_TAP2_L: JCH2.b7, JSEND2.b1
SEND_TAP2_R: JCH2.b8, JSEND2.b2
SEND_TAP3_L: JCH3.b7, JSEND3.b1
SEND_TAP3_R: JCH3.b8, JSEND3.b2
SEND_TAP4_L: JCH4.b7, JSEND4.b1
SEND_TAP4_R: JCH4.b8, JSEND4.b2

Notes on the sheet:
SLOT CH1 (canale)
SLOT SEND1 (fx-send)
SLOT CH2 (canale)
SLOT SEND2 (fx-send)
SLOT CH3 (canale)
SLOT SEND3 (fx-send)
SLOT CH4 (canale)
SLOT SEND4 (fx-send)
SLOT FIL1 (filtro)
SLOT FIL2 (filtro)
CAVO C1
CAVO C2
CAVO C3
CAVO C4
POTENZA P2
